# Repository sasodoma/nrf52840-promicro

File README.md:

# nRF52840 ProMicro

The nRF52840 ProMicro board is also known as the SuperMini board. It's a clone of the nice!nano board with a mix of v1 and v2 design features. The schematic is available online, albeit with a small mistake, but I was unable to find board design files. The aim of this repository is to reverse engineer the board design and determine which component is which so that I can desolder them from the board and reuse them on my custom PCB.

# Schematic
This is the original schematic as posted on https://chat.nologo.tech/d/80. The voltage divider for the battery is marked as being connected to P0.04, which is an analog input pin. On the actual board it's connected to P0.24 instead, which makes it unsuitable for battery voltage measurements. Instead you can measure the battery directly on VDDH pin, but the voltage will rise when USB is plugged in. To prevent this incorrect reading, you can remove the NPQ2, NBD1 and NPR7 components, and instead bridge pins 3 and 2 on the NPQ2 MOSFET. This way the nRF chip will always draw power from the battery and USB will only charge the battery and thus power the board indirectly. The voltage on VDDH will then be the actual voltage of the battery (slightly higher while charging but it won't jump to 100%). This could be problematic if your board consumed more current than the charger provided, and the battery would discharge while plugged in, so keep that in mind.

# Sleep current problems
I wanted to use these boards to create some low power BTHome sensors. I have boards from many different sources. Some exhibit great power consumption, only 4 uA in sleep, with EXTVCC disabled. Others had a consumption of 60 uA, which is still pretty good but it's 15x more. After some component swapping, I found the problem to be the W5 marked diode. This is supposed to be a BAT60B Schottky diode, with a voltage drop of 0.24 V. On the high power consumption boards I instead measured a drop of 0.7 V, indicating a regular silicon diode. What's more concerning is that apparently the reverse leakage current of this diode was also much worse and this is what was causing the power consumption.

# Clock issues

On many boards, the load capacitors on the 32.768 kHz crystal are likely the wrong value, so the RTC runs at the wrong frequency. Of five boards tested from one manufacturer, the worst had a frequency offset of 160 ppm and the others 50–70 ppm. For comparison, crystals are typically specified at ±20 ppm. Incorrect loading can also make the frequency unstable. Depending on the application, this may be a problem, so it is worth noting.

# KiCad project
The project in the KiCad folder is my attempt at replicating the board to identify every component's location. The USB connector is not the correct footprint, but the name in the schematic is correct. KiCad doesn't seem to have a footprint for the antenna, but the model is CA-C03.

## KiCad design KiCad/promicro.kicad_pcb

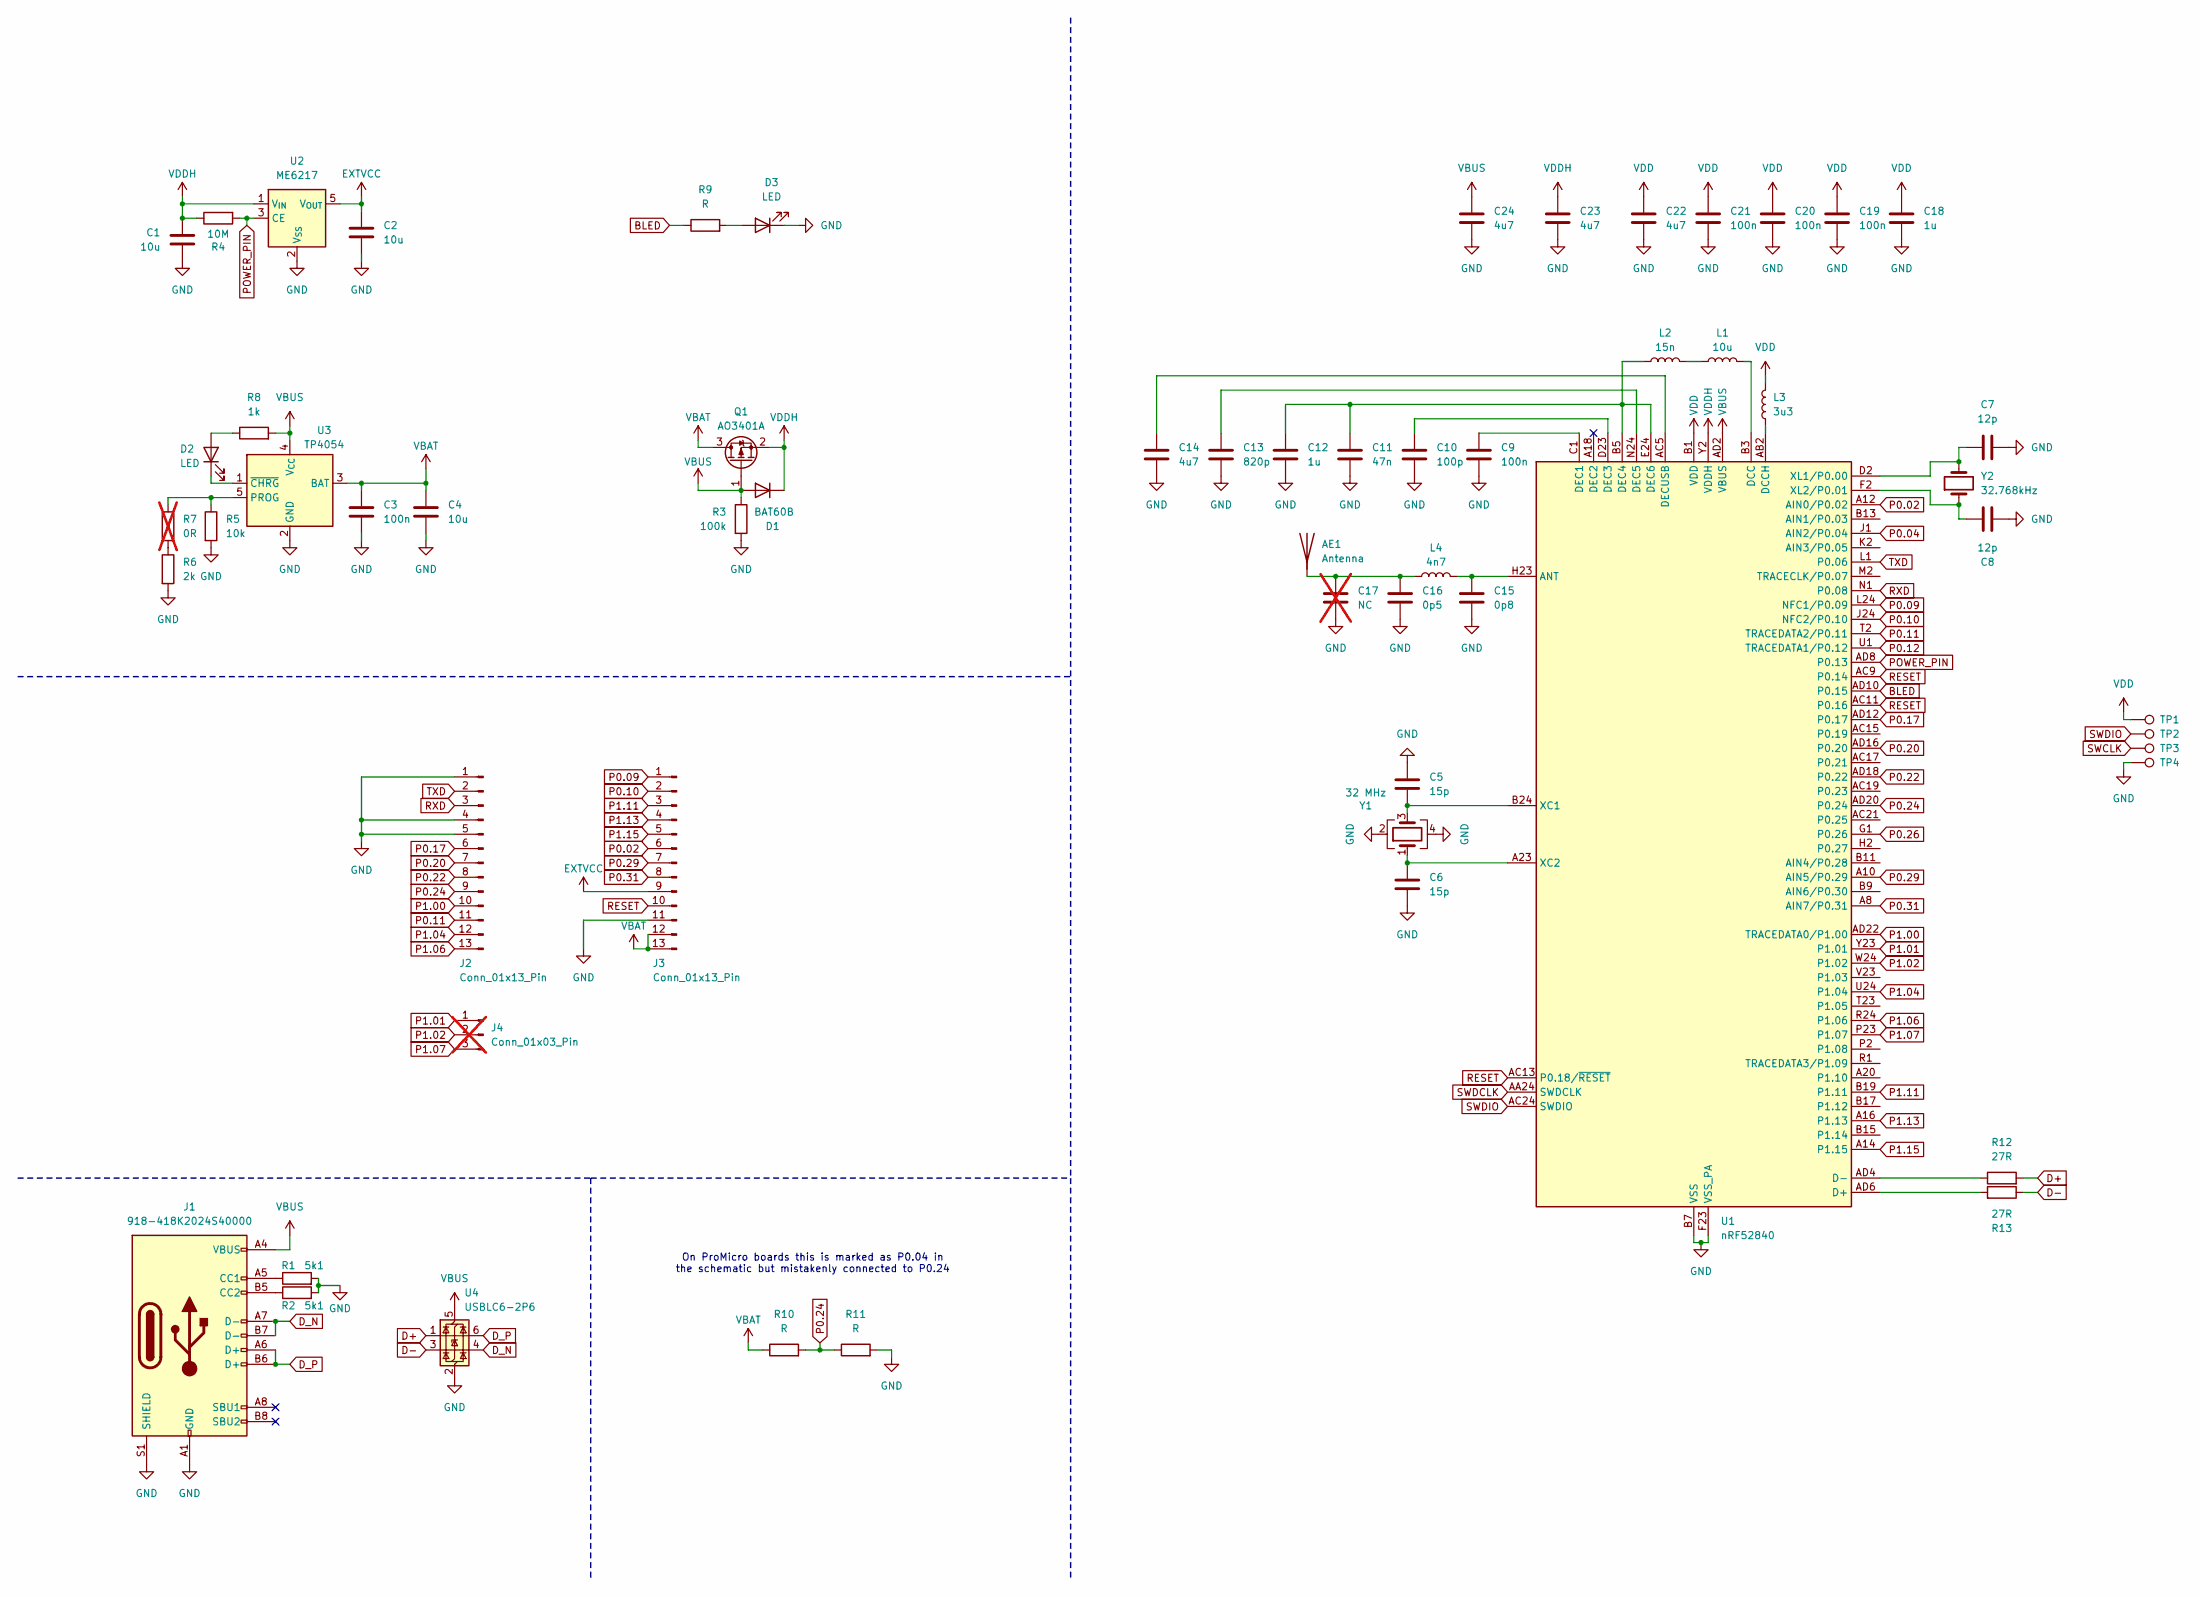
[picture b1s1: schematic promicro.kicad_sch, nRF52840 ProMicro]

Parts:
AE1: Antenna
C1, C2, C4: 10u; C_0402_1005Metric
C3, C9, C19, C20, C21: 100n; C_0201_0603Metric
C5, C6: 15p; C_0402_1005Metric
C7, C8: 12p; C_0402_1005Metric
C10: 100p; C_0402_1005Metric
C11: 47n; C_0402_1005Metric
C12: 1u; C_0402_1005Metric
C13: 820p; C_0402_1005Metric
C14, C22, C23, C24: 4u7; C_0402_1005Metric
C15: 0p8; C_0402_1005Metric
C16: 0p5; C_0402_1005Metric
C17: NC; C_0402_1005Metric; not fitted
C18: 1u; C_0201_0603Metric
D1: BAT60B; D_SOD-323
D2, D3: LED; LED_0603_1608Metric
J1: 918-418K2024S40000; USB_C_Receptacle_GCT_USB4105-xx-A_16P_TopMnt_Horizontal
J2, J3: Conn_01x13_Pin; PinHeader_1x13_P2.54mm_Vertical
J4: Conn_01x03_Pin; PinHeader_1x03_P2.54mm_Vertical; not fitted
L1: 10u; L_0402_1005Metric
L2: 15n; L_0402_1005Metric
L3: 3u3; L_0402_1005Metric
L4: 4n7; L_0402_1005Metric
Q1: AO3401A; SOT-23
R1, R2: 5k1; R_0201_0603Metric
R3: 100k; R_0402_1005Metric
R4: 10M; R_0201_0603Metric
R5: 10k; R_0402_1005Metric
R6: 2k; R_0402_1005Metric
R7: 0R; R_0603_1608Metric; not fitted
R8: 1k; R_0201_0603Metric
R9, R10, R11: R; R_0201_0603Metric
R12, R13: 27R; R_0201_0603Metric
TP1, TP2, TP3, TP4: TestPoint; TestPoint_Pad_1.0x1.0mm
U1: nRF52840; Nordic_AQFN-73-1EP_7x7mm_P0.5mm
U2: ME6217; SOT-23-5
U3: TP4054; TSOT-23-5
U4: USBLC6-2P6; SOT-666
Y1: 32 MHz; Crystal_SMD_3225-4Pin_3.2x2.5mm
Y2: 32.768kHz; Crystal_SMD_G8-2Pin_3.2x1.5mm

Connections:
BLED: R9.1, U1.AD10 (P0.15)
D+: R12.2, U4.1 (I/O1)
D-: R13.1, U4.3 (I/O2)
D_N: J1.A7 (D-), J1.B7 (D-), U4.4 (I/O2)
D_P: J1.A6 (D+), J1.B6 (D+), U4.6 (I/O1)
EXTVCC: C2.1, J3.9, U2.5 (V_{OUT})
GND: C1.2, C2.2, C3.2, C4.2, C5.1, C6.2, C7.2, C8.2, C9.2, C10.2, C11.2, C12.2, C13.2, C14.2, C15.2, C16.2, C17.2, C18.2, C19.2, C20.2, C21.2, C22.2, C23.2, C24.2, D3.1 (K), J1.A1 (GND), J1.A12 (GND), J1.B1 (GND), J1.B12 (GND), J1.S1 (SHIELD), J2.1, J2.4, J2.5, J3.11, R1.2, R2.2, R3.2, R5.2, R6.2, R11.2, TP4.1, U1.B7 (VSS), U1.EP (VSS), U1.F23 (VSS_PA), U2.2 (V_{SS}), U3.2 (GND), U4.2 (GND), Y1.2, Y1.4
unnamed: AE1.1, C16.1, C17.1, L4.1
unnamed: D2.2 (A), R8.1
unnamed: D2.1 (K), U3.1 (~CHRG)
unnamed: D3.2 (A), R9.2
unnamed: J1.A5 (CC1), R1.1
unnamed: J1.B5 (CC2), R2.1
unnamed: L1.1, L2.2
unnamed: R6.1, R7.2
unnamed: C15.1, L4.2, U1.H23 (ANT)
unnamed: R13.2, U1.AD6 (D+)
unnamed: R12.1, U1.AD4 (D-)
unnamed: L1.2, U1.B3 (DCC)
unnamed: L3.1, U1.AB2 (DCCH)
unnamed: C9.1, U1.C1 (DEC1)
unnamed: C10.1, U1.D23 (DEC3)
unnamed: C11.1, C12.1, L2.1, U1.B5 (DEC4), U1.E24 (DEC6)
unnamed: C13.1, U1.N24 (DEC5)
unnamed: C14.1, U1.AC5 (DECUSB)
unnamed: C5.2, U1.B24 (XC1), Y1.3
unnamed: C6.1, U1.A23 (XC2), Y1.1
unnamed: C7.1, U1.D2 (XL1/P0.00), Y2.2
unnamed: C8.1, U1.F2 (XL2/P0.01), Y2.1
unnamed: R5.1, R7.1, U3.5 (PROG)
P0.02: J3.6, U1.A12 (AIN0/P0.02)
P0.04: U1.J1 (AIN2/P0.04)
P0.09: J3.1, U1.L24 (NFC1/P0.09)
P0.10: J3.2, U1.J24 (NFC2/P0.10)
P0.11: J2.11, U1.T2 (TRACEDATA2/P0.11)
P0.12: U1.U1 (TRACEDATA1/P0.12)
P0.17: J2.6, U1.AD12 (P0.17)
P0.20: J2.7, U1.AD16 (P0.20)
P0.22: J2.8, U1.AD18 (P0.22)
P0.24: J2.9, R10.2, R11.1, U1.AD20 (P0.24)
P0.26: U1.G1 (P0.26)
P0.29: J3.7, U1.A10 (AIN5/P0.29)
P0.31: J3.8, U1.A8 (AIN7/P0.31)
P1.00: J2.10, U1.AD22 (TRACEDATA0/P1.00)
P1.01: J4.1, U1.Y23 (P1.01)
P1.02: J4.2, U1.W24 (P1.02)
P1.04: J2.12, U1.U24 (P1.04)
P1.06: J2.13, U1.R24 (P1.06)
P1.07: J4.3, U1.P23 (P1.07)
P1.11: J3.3, U1.B19 (P1.11)
P1.13: J3.4, U1.A16 (P1.13)
P1.15: J3.5, U1.A14 (P1.15)
POWER_PIN: R4.2, U1.AD8 (P0.13), U2.3 (CE)
RESET: J3.10, U1.AC9 (P0.14), U1.AC11 (P0.16), U1.AC13 (P0.18/~RESET)
RXD: J2.3, U1.N1 (P0.08)
SWCLK: TP3.1
SWDCLK: U1.AA24 (SWDCLK)
SWDIO: TP2.1, U1.AC24 (SWDIO)
TXD: J2.2, U1.L1 (P0.06)
VBAT: C3.1, C4.1, J3.12, J3.13, Q1.3 (D), R10.1, U3.3 (BAT)
VBUS: C24.1, D1.2 (A), J1.A4 (VBUS), J1.A9 (VBUS), J1.B4 (VBUS), J1.B9 (VBUS), Q1.1 (G), R3.1, R8.2, U1.AD2 (VBUS), U3.4 (V_{CC}), U4.5 (VBUS)
VDD: C18.1, C19.1, C20.1, C21.1, C22.1, L3.2, TP1.1, U1.A22 (VDD), U1.AD14 (VDD), U1.AD23 (VDD), U1.B1 (VDD), U1.W1 (VDD)
VDDH: C1.1, C23.1, D1.1 (K), Q1.2 (S), R4.1, U1.Y2 (VDDH), U2.1 (V_{IN})

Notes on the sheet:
On ProMicro boards this is marked as P0.04 in the schematic but mistakenly connected to P0.24

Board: 2 copper layers, 59 parts (7 on the bottom side), 58 nets, no tracks yet.

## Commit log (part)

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2025-07-26 Add images
2025-07-26 Add schematic
2025-07-26 Crop the image
2025-07-26 Add KiCad project
2025-10-03 Document sleep current problems and diode findings
    Added section on sleep current problems and diode issues.
2025-10-06 Update README with battery measurement instructions
    Expanded explanation of the schematic and battery voltage measurement adjustments.
2025-10-23 Fix USB pins
